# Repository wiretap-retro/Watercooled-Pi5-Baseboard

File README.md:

# Watercooled Pi5 Baseboard
A baseboard for setting up a watercooled Raspberry Pi 5.

\

\

## Info
In this repository you'll find my Watercooled Raspberry Pi 5 baseboard. It features mounts for the Raspberry Pi 2/3/4/5, an Arduino Nano, and a 120mm fan/radiator. The baseboard is powered through the 5.5x2.1mm 12V barrel jack, which powers the pump, fan, and Arduino. There is an onboard 4A fuse for protection. The Pi is powered separate with its own USB power input.\
\
The Arduino is used for the PWM fan and pump control so it leaves the entire Pi header available for hat use. \
\
Arduino Nano connections:\
A0: Pump Adjustment 10k trim pot input \
A1: Fan Adjustment 10k trim pot input \
A4: SDA for OLED screen (SSD1306 model) \
A5: SCL for OLED screen (SSD1306 model) \
D2: Pump tachometer input \
D6: Fan tachometer input \
D9: PWM pump demand output \
D10: PWM fan demand output
\
\
For the radiator and fan, you'll want to use some generic standoffs commonly found on Aliexpress, Amazon, or Ebay. These will all depend on your fan and radiator choices for what fits best. A M3 5mm standoff provides a sufficient gap between the board and radiator to allow airflow to pass through. After all, watercooling even a Raspberry Pi 5 is pointless and passive cooling alone is enough at the factory clockspeed. 

## Code
I have uploaded some sample code for you. When designing the board, I stupidly designed the tach pins where only one of the ports has an interrupt capability. This requires using the PinChangeInterrupts library. I have attached the settings file for you to overwrite the one that is automatically downloaded, then it will properly display the fan tachometer. This code is fully tested working for fan and pump control.
\
See picture below for the screen layout:
\
\

## License
UNLICENSE -- do what you want with it.

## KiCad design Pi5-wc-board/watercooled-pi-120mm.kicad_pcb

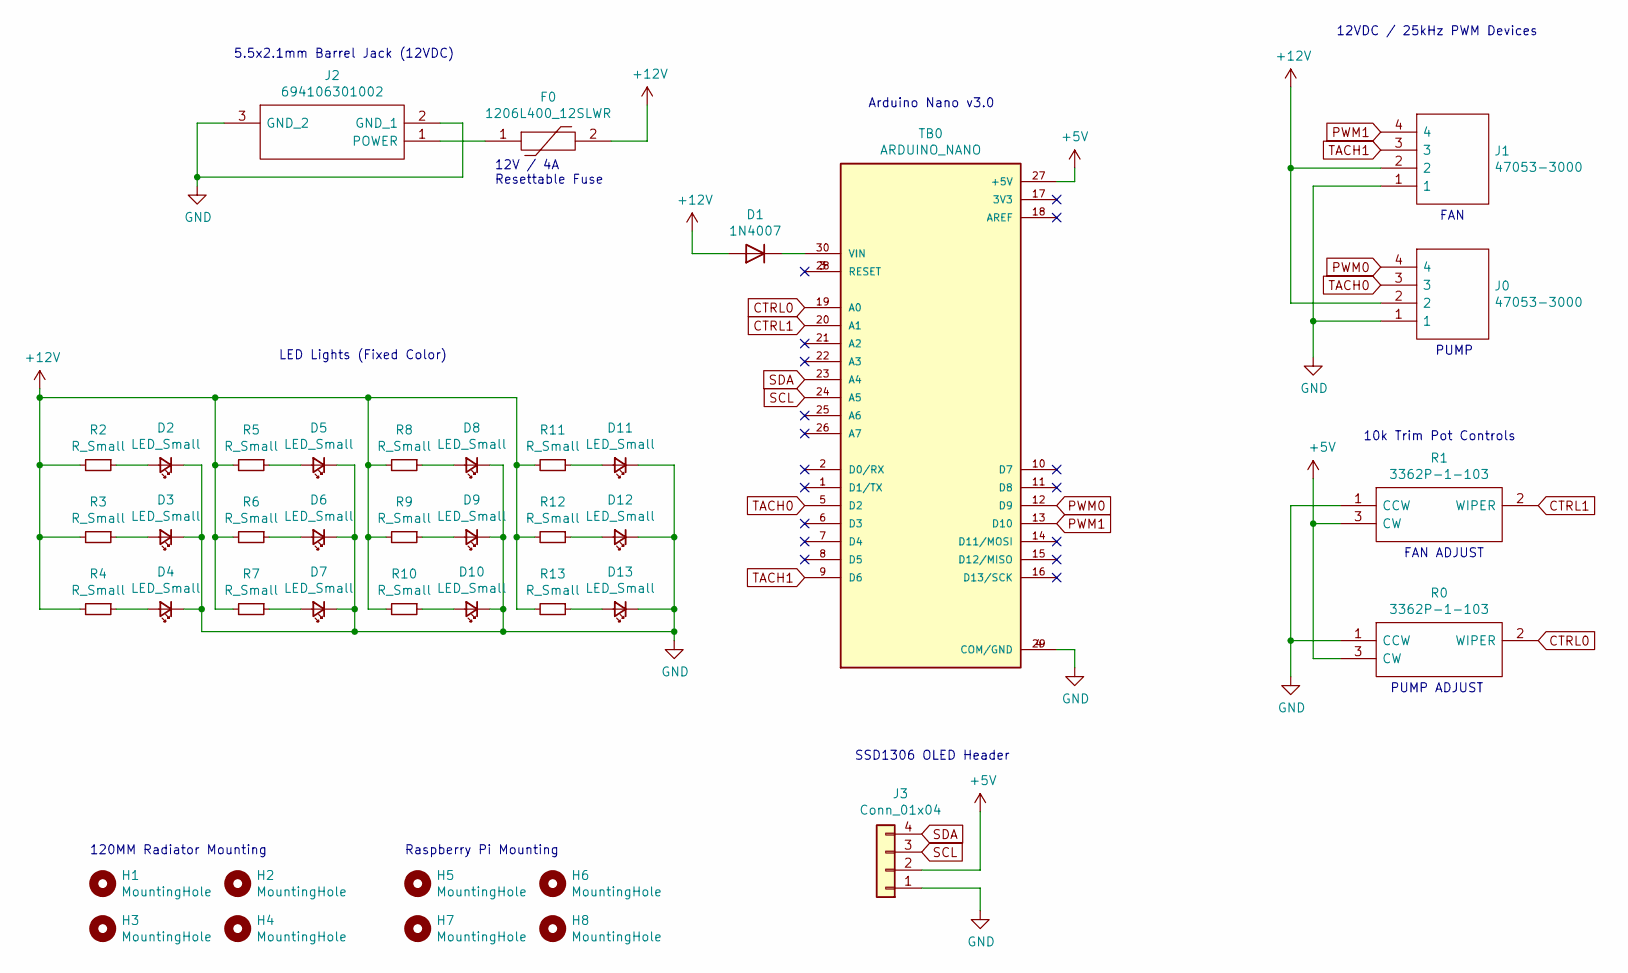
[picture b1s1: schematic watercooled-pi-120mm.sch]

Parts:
D1: 1N4007; D_DO-41_SOD81_P10.16mm_Horizontal
D2, D3, D4, D5, D6, D7, D8, D9, D10, D11, D12, D13: LED_Small; LED_0805_2012Metric_Pad1.15x1.40mm_HandSolder
F0: 1206L400_12SLWR; 1206L075SLYR; Mouser Part Number 576-1206L400/12SLWR
H1, H2, H3, H4: MountingHole; MountingHole_3.2mm_M3
H5, H6, H7, H8: MountingHole; MountingHole_2.7mm_M2.5
J0, J1: 47053-3000; 470533000; Mouser Part Number 538-47053-3000
J2: 694106301002; 694106301002_1; Mouser Part Number 710-694106301002
J3: Conn_01x04; PinSocket_1x04_P2.54mm_Vertical
R0, R1: 3362P-1-103; 3362P_1; Mouser Part Number 652-3362P-1-103
R2, R3, R4, R5, R6, R7, R8, R9, R10, R11, R12, R13: R_Small; R_0805_2012Metric_Pad1.15x1.40mm_HandSolder
TB0: ARDUINO_NANO; Arduino_Nano_Socket

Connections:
+5V: J3.2, R0.3 (CW), R1.3 (CW), TB0.27 (+5V)
+12V: D1.2 (A), F0.2, J0.2, J1.2, R2.2, R3.2, R4.2, R5.2, R6.2, R7.2, R8.2, R9.2, R10.2, R11.2, R12.2, R13.2
CTRL0: R0.2 (WIPER), TB0.19 (A0)
CTRL1: R1.2 (WIPER), TB0.20 (A1)
GND: D2.1 (K), D3.1 (K), D4.1 (K), D5.1 (K), D6.1 (K), D7.1 (K), D8.1 (K), D9.1 (K), D10.1 (K), D11.1 (K), D12.1 (K), D13.1 (K), J0.1, J1.1, J2.2 (GND_1), J2.3 (GND_2), J3.1, R0.1 (CCW), R1.1 (CCW), TB0.4 (COM/GND), TB0.29 (COM/GND)
unnamed: D1.1 (K), TB0.30 (VIN)
unnamed: D2.2 (A), R2.1
unnamed: D3.2 (A), R3.1
unnamed: D4.2 (A), R4.1
unnamed: D5.2 (A), R5.1
unnamed: D6.2 (A), R6.1
unnamed: D7.2 (A), R7.1
unnamed: D8.2 (A), R8.1
unnamed: D9.2 (A), R9.1
unnamed: D10.2 (A), R10.1
unnamed: D11.2 (A), R11.1
unnamed: D12.2 (A), R12.1
unnamed: D13.2 (A), R13.1
unnamed: F0.1, J2.1 (POWER)
unnamed: TB0.3 (RESET), TB0.28 (RESET)
PWM0: J0.4, TB0.12 (D9)
PWM1: J1.4, TB0.13 (D10)
SCL: J3.3, TB0.24 (A5)
SDA: J3.4, TB0.23 (A4)
TACH0: J0.3, TB0.5 (D2)
TACH1: J1.3, TB0.9 (D6)

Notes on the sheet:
FAN
PUMP
12VDC / 25kHz PWM Devices
Arduino Nano v3.0
FAN ADJUST
PUMP ADJUST
10k Trim Pot Controls
12V / 4A Resettable Fuse
5.5x2.1mm Barrel Jack (12VDC)
SSD1306 OLED Header
120MM Radiator Mounting
Raspberry Pi Mounting
LED Lights (Fixed Color)

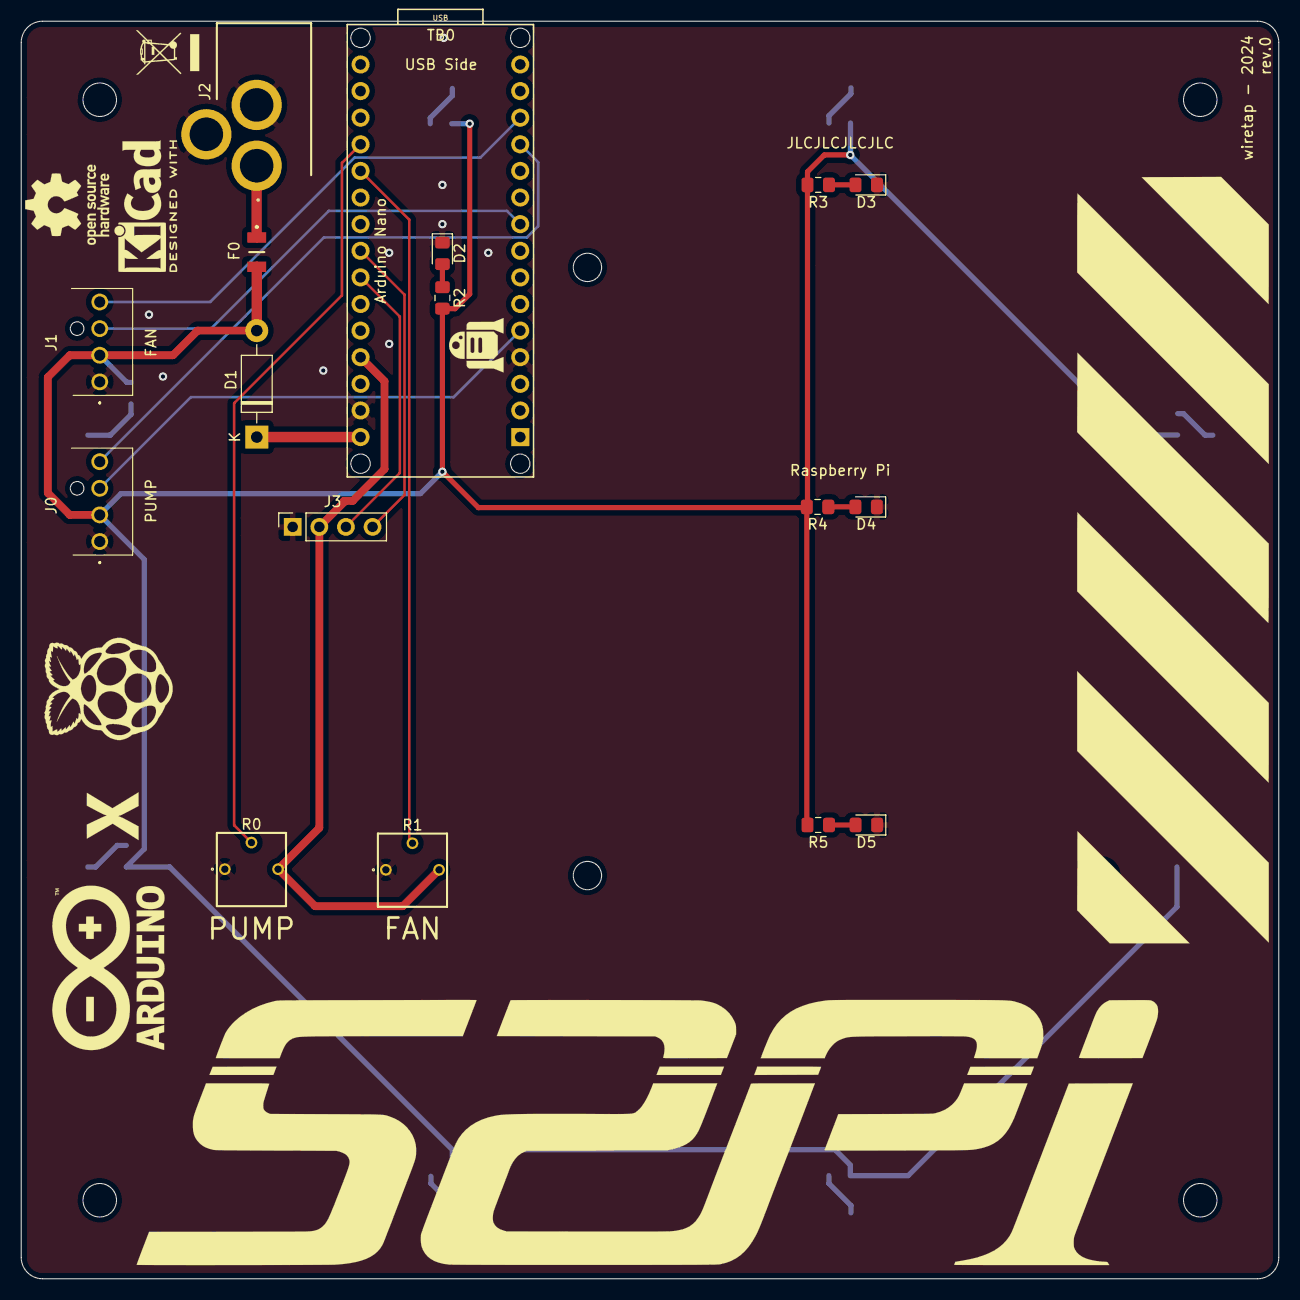
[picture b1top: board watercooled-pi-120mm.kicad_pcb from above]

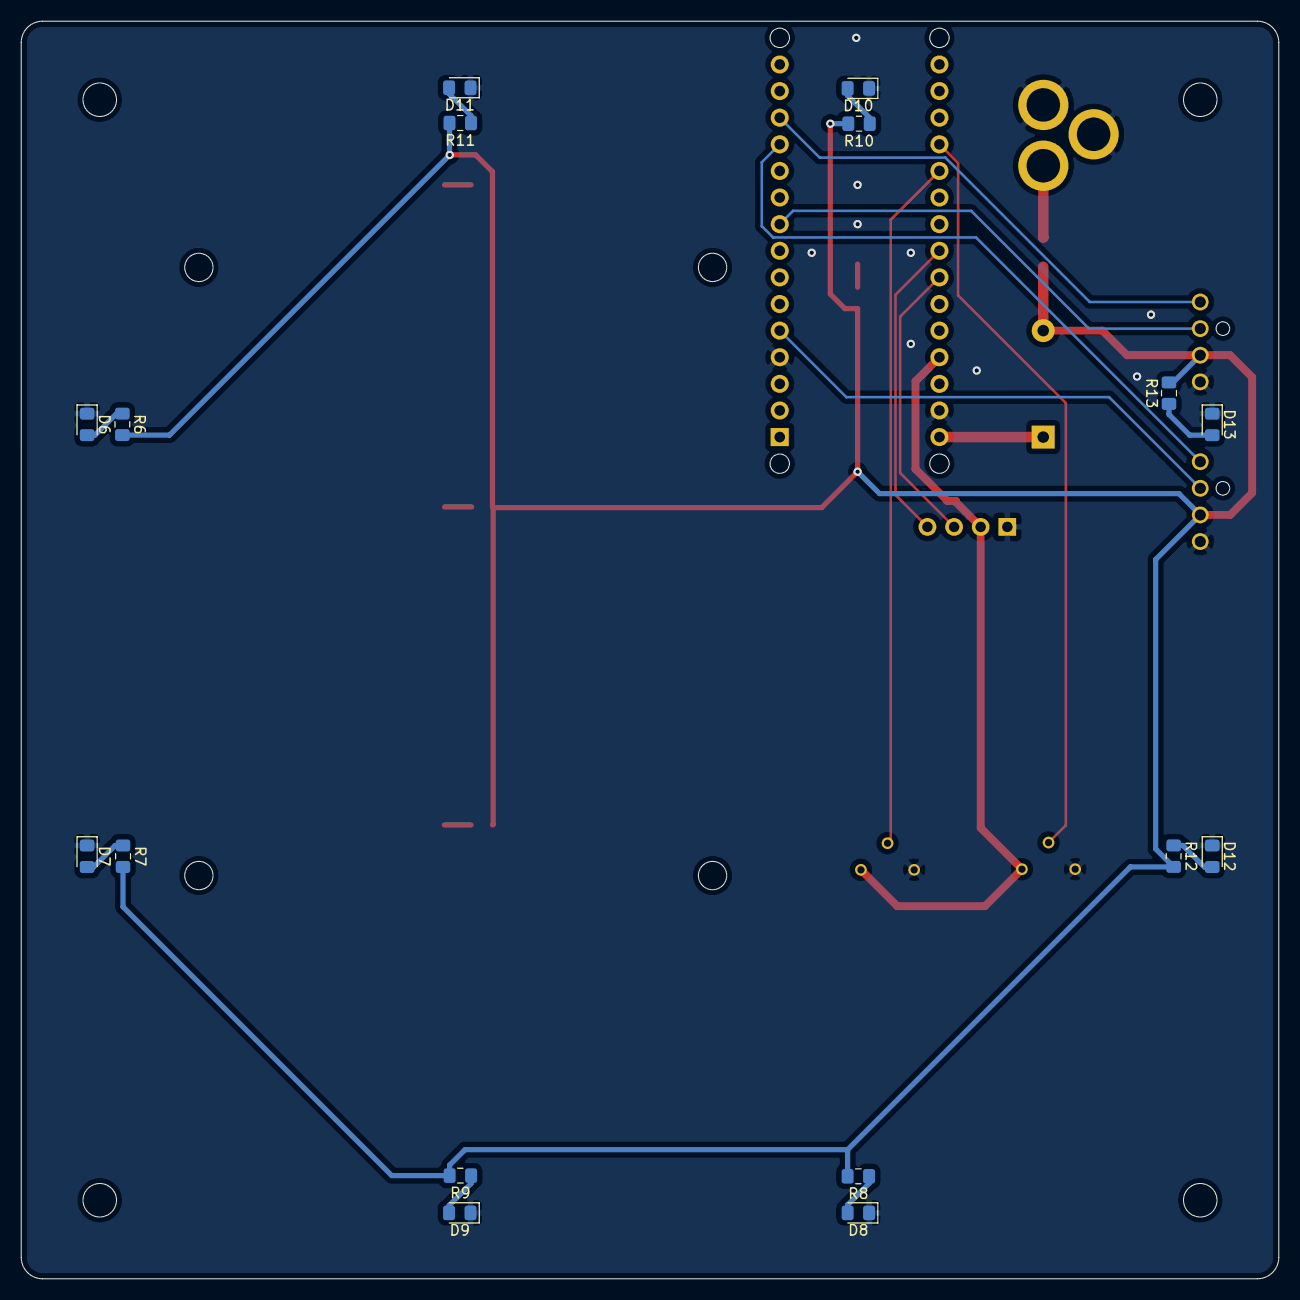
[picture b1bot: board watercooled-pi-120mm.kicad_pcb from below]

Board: 2 copper layers, 120.0 x 120.0 mm, 41 parts (16 on the bottom side), 26 nets.

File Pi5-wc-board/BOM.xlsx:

Reference | Quantity | Value | Footprint | Manufacturer | Part Number | Mouser Part Number | Notes
D1 | 1 | 1N4007 | Diode_THT:D_DO-41_SOD81_P10.16mm_Horizontal | Diotec Semiconductor | 1N4007 | 637-1N4007
D2 D3 D4 D5 D6 D7 D8 D9 D10 D11 D12 D13 | 12 | LED_Small | LED_SMD:LED_0805_2012Metric_Pad1.15x1.40mm_HandSolder |  |  |  | Any 0805 SMD LED
F0 | 1 | 1206L400_12SLWR | 1206L075SLYR | LITTELFUSE | 1206L400/12SLWR | 576-1206L400/12SLWR
J1 J0 | 2 | 47053-3000 | 470533000 | Molex | 47053-3000 | 538-47053-3000
J2 | 1 | 694106301002 | 694106301002_1 | Wurth Elektronik | 694106301002 | 710-694106301002
J3 | 1 | Conn_01x04 | Connector_PinSocket_2.54mm:PinSocket_1x04_P2.54mm_Vertical | Harwin | M20-7820446 | 855-M20-7820446
R1 R0 | 2 | 3362P-1-103 | 3362P_1 | Bourns | 3362P-1-103 | 652-3362P-1-103
R2 R3 R4 R5 R6 R7 R8 R9 R10 R11 R12 R13 | 12 | R_Small | Resistor_SMD:R_0805_2012Metric_Pad1.15x1.40mm_HandSolder |  |  |  | 0805 SMD resistor appropriate for your LEDs (i.e. 1k)
TB0 | 1 | ARDUINO_NANO | SamacSys_Parts:Arduino_Nano_Socket | Arduino | Nano |  | Arduino Nano header is optional -- can direct solder

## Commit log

2025-02-18 Create LICENSE
